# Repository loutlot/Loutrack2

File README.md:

# Loutrack2

Loutrack2 is an open-source optical motion tracking stack built around Raspberry Pi camera nodes, host-side calibration tools, and a GUI workflow that is already practical for multi-camera bring-up and tracking experiments.

日本語はこちら: [README_ja.md](README_ja.md)

## What It Is

Loutrack2 combines:

- Raspberry Pi camera capture nodes for reflective marker observation
- host-side control, calibration, and inspection tools
- multi-camera 3D reconstruction and tracking
- a GUI-first workflow for setup, tuning, capture, and review

This repository is aimed at people who want to build, understand, and extend a DIY camera-based tracking system in the open. The current project is strongest in camera bring-up, calibration, and live tracking inspection.

## What Works Today

- Pi capture nodes detect reflective blobs and stream observations to the host
- the host GUI covers blob tuning, mask building, pose capture, floor or metric capture, and extrinsics generation
- intrinsics and extrinsics outputs are generated as JSON artifacts
- synchronized camera observations are reconstructed into 3D marker positions
- the 3D Tracking page shows scene state, camera health, stream diagnostics, and live rigid-body status
- custom rigid bodies can be registered or removed directly from triangulated blobs in the tracking viewer

## System Overview

```mermaid
flowchart LR
  subgraph PiCameras["Raspberry Pi Camera Nodes"]
    A["pi-cam-01<br/>capture_runtime.py"]
    B["pi-cam-02+<br/>capture_runtime.py"]
    C["Blob detection<br/>Mask / Preview / UDP streaming"]
  end

  subgraph Host["Host Workstation"]
    D["loutrack_gui.py<br/>Web GUI"]
    E["UDPReceiver"]
    F["Calibration session"]
    G["Intrinsics / Extrinsics tools"]
    H["Tracking runtime"]
    I["3D reconstruction"]
  end

  subgraph Outputs["Outputs"]
    J["Intrinsics JSON"]
    K["Extrinsics JSON"]
    L["3D marker positions"]
    M["Tracking scene snapshot"]
  end

  A -->|UDP frames| E
  B -->|UDP frames| E
  D -->|TCP control| A
  D -->|TCP control| B
  E --> F
  F --> G
  G --> J
  G --> K
  E --> H
  H --> I
  I --> L
  H --> M
```

## Workflow

The current Loutrack2 experience is centered on a single GUI flow from camera startup to live tracking review.

Typical flow:

1. Start the Pi capture nodes
2. Open the host GUI
3. Tune blob detection
4. Build masks
5. Capture pose data
6. Capture floor or metric data
7. Generate extrinsics
8. Start tracking and inspect the reconstructed scene

The startup and shutdown procedure for Pi nodes and the GUI lives at [`docs/30_procedure/pi_gui_start_stop.md`](docs/30_procedure/pi_gui_start_stop.md).

## Tracking View

The 3D Tracking page is one of the clearest expressions of the project's current direction: operational feedback is visible, rigid bodies can be inspected live, and the scene is meant to be understandable while the system is running.

Current highlights:

- live tracking start and stop feedback is surfaced in the GUI
- camera health, latency, and stream diagnostics stay visible beside the scene
- the epipolar gate is adjustable from Tracking Control
- host tracking pairs frames with a fixed `4237us` half-frame window at `118fps`
- the old host-side sync-quality dashboard is gone, keeping tracking focused on scene and camera health
- custom rigid-body registration works directly from triangulated blobs

## Hardware Direction

Loutrack2 also includes an open hardware direction centered around reproducible DIY tracking camera nodes and tracked targets.

Current hardware direction:

- Raspberry Pi-based camera nodes built from commonly available parts
- Raspberry Pi Camera Module 3 Wide NoIR as the current camera baseline
- PoE HAT-based power and networking over a single LAN cable
- a custom board mounted above the Pi that combines camera holding and IR LED illumination
- open hardware files in the repository, including PCB design data and 3D-printable parts
- reflective tracked markers built from 3D-printed spheres and retroreflective tape

Relevant repository areas:

- [`hardware`](hardware) for printable parts and board-related assets
- [`hardware/LED board`](hardware/LED%20board) for the custom LED board design files
- [`hardware/pi mount`](hardware/pi%20mount) for Pi mount printable parts

## Project Direction

Loutrack2 is already useful as a multi-camera optical tracking foundation, but it is still a builder-oriented platform rather than a finished end-user full-body tracker.

The next direction includes:

- more stable rigid-body clustering and identity tracking
- body-part level tracking for head, chest, waist, and feet
- more reliable rigid-body association through the full pipeline
- IK-friendly pose output
- SteamVR tracker output
- continued improvements to deployment, setup, and hardware documentation

## Open Source

Loutrack2 is being developed in the open.

- pull requests are welcome
- forks and experiments are welcome
- documentation, setup improvements, hardware refinements, and calibration workflow improvements are especially useful

## License

This project is intended to be released under `GPL-3.0-or-later`.

## Repository Map

- [`src/pi`](src/pi) for Raspberry Pi capture services
- [`src/deploy`](src/deploy) for Raspberry Pi code deployment, service installation, and rollback helpers
- [`src/host`](src/host) for the host GUI, receiver, runtime, and tracking pipeline
- [`src/camera-calibration`](src/camera-calibration) for intrinsics and extrinsics tooling
- [`src/calibration`](src/calibration) for calibration domain types and targets
- [`calibration`](calibration) for generated calibration artifacts
- [`docs/30_procedure`](docs/30_procedure) for Pi / GUI startup, verification, and shutdown procedures
- [`schema`](schema) for message and control contracts
- [`tests`](tests) for regression coverage

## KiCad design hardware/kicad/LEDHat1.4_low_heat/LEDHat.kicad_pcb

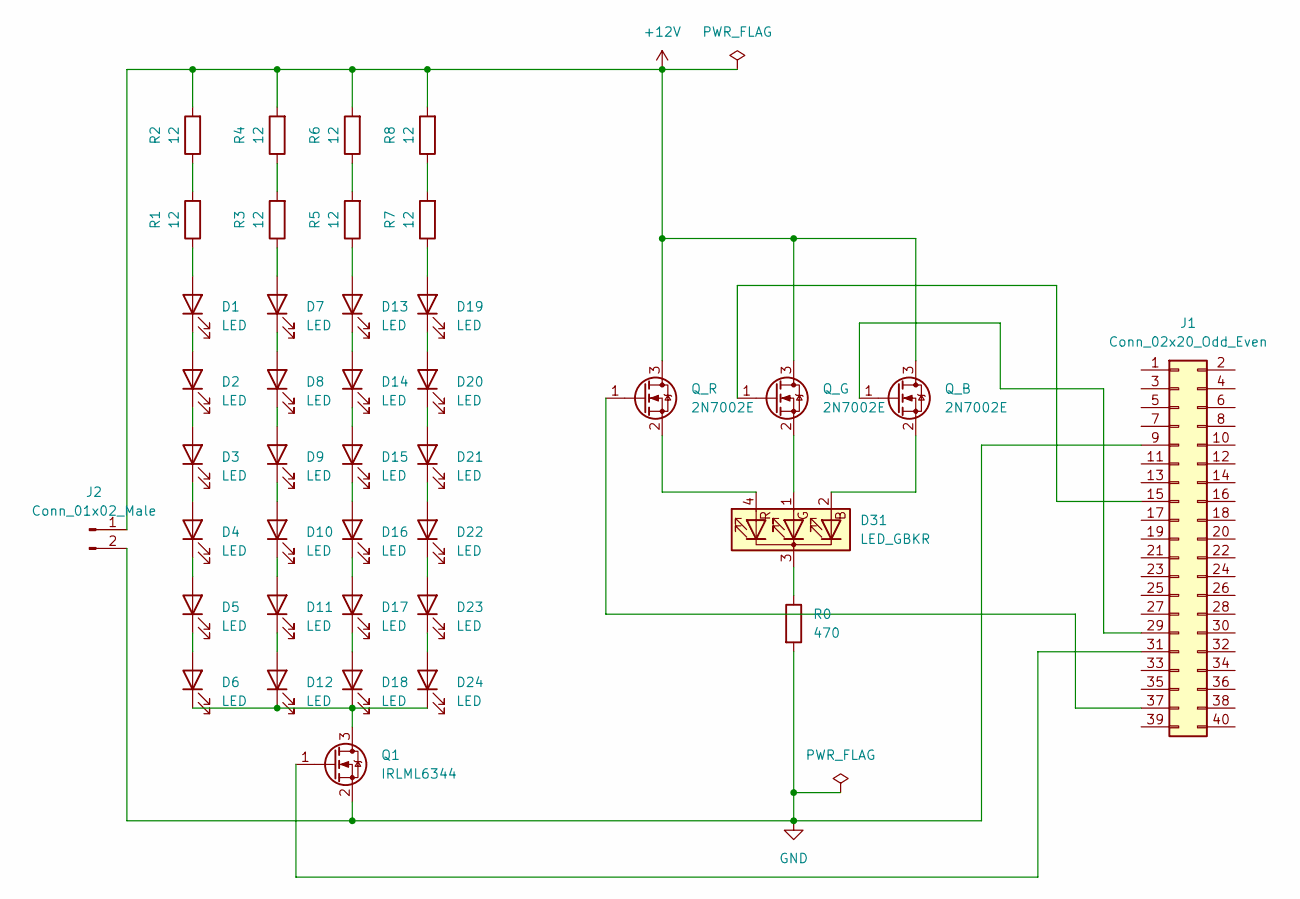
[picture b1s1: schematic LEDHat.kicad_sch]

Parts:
D1, D2, D3, D4, D5, D6, D7, D8, D9, D10, D11, D12, D13, D14, D15, D16, D17, D18, D19, D20, D21, D22, D23, D24: LED; LED_PLCC_2835_Handsoldering
D31: LED_GBKR; LED_D5.0mm-4_RGB_Staggered_Pins
J1: Conn_02x20_Odd_Even; PinSocket_2x20_P2.54mm_Vertical
J2: Conn_01x02_Male; PinHeader_1x02_P2.54mm_Horizontal
Q1: IRLML6344; SOT-23
Q_B: 2N7002E; SOT-23
Q_G: 2N7002E; SOT-23
Q_R: 2N7002E; SOT-23
R0: 470; R_Axial_DIN0207_L6.3mm_D2.5mm_P7.62mm_Horizontal
R1, R2, R3, R4, R5, R6, R7, R8: 12; R_Axial_DIN0207_L6.3mm_D2.5mm_P7.62mm_Horizontal

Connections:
+12V: J2.1, Q_B.3 (D), Q_G.3 (D), Q_R.3 (D), R2.2, R4.2, R6.2, R8.2
GND: J1.9, J2.2, Q1.2 (S), R0.2
unnamed: D1.1 (K), D2.2 (A)
unnamed: D1.2 (A), R1.1
unnamed: D2.1 (K), D3.2 (A)
unnamed: D3.1 (K), D4.2 (A)
unnamed: D4.1 (K), D5.2 (A)
unnamed: D5.1 (K), D6.2 (A)
unnamed: D7.1 (K), D8.2 (A)
unnamed: D7.2 (A), R3.1
unnamed: D8.1 (K), D9.2 (A)
unnamed: D10.1 (K), D11.2 (A)
unnamed: D9.1 (K), D10.2 (A)
unnamed: D11.1 (K), D12.2 (A)
unnamed: D6.1 (K), D12.1 (K), D18.1 (K), D24.1 (K), Q1.3 (D)
unnamed: D13.1 (K), D14.2 (A)
unnamed: D13.2 (A), R5.1
unnamed: D14.1 (K), D15.2 (A)
unnamed: D15.1 (K), D16.2 (A)
unnamed: D16.1 (K), D17.2 (A)
unnamed: D17.1 (K), D18.2 (A)
unnamed: D19.1 (K), D20.2 (A)
unnamed: D19.2 (A), R7.1
unnamed: D20.1 (K), D21.2 (A)
unnamed: D21.1 (K), D22.2 (A)
unnamed: D22.1 (K), D23.2 (A)
unnamed: D23.1 (K), D24.2 (A)
unnamed: D31.1 (GA), Q_G.2 (S)
unnamed: D31.2 (BA), Q_B.2 (S)
unnamed: D31.3 (K), R0.1
unnamed: D31.4 (RA), Q_R.2 (S)
unnamed: J1.15, Q_G.1 (G)
unnamed: J1.29, Q_B.1 (G)
unnamed: J1.31, Q1.1 (G)
unnamed: J1.37, Q_R.1 (G)
unnamed: R1.2, R2.1
unnamed: R3.2, R4.1
unnamed: R5.2, R6.1
unnamed: R7.2, R8.1

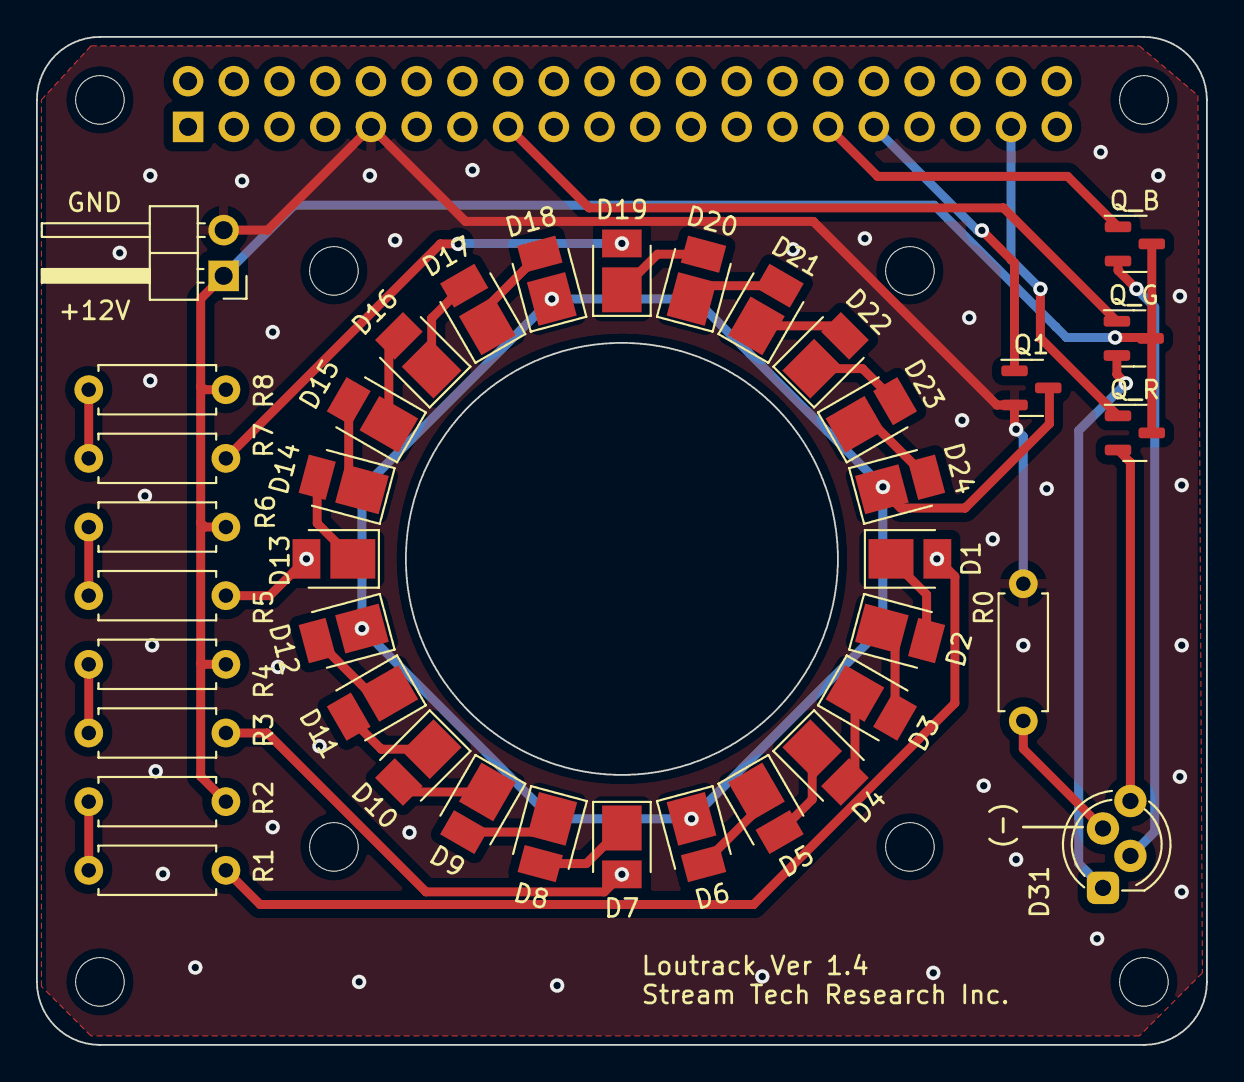
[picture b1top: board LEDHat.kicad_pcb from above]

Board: 2 copper layers, 65.0 x 56.0 mm, 40 parts (1 on the bottom side), 39 nets.

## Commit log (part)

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2026-02-22 chore: initial commit
2026-02-22 refactor: enhance Pi capture service and update control commands
    - Improved the Pi capture service in `src/pi/capture.py` for better performance.
    - Added new control commands (reset, get_status) in `src/host/control.py`.
    - Updated documentation to include new commands and usage examples.
2026-02-24 docs: remove outdated Pi service integration details from README and clean up hosts.ini comments
2026-03-07 feat: add wand session orchestration and next-step runbook
2026-03-08 feat: update default camera ID handling in capture service
    - Changed the default value of `camera_id` in `src/pi/capture.py` to derive from the device name using `hostnamectl` or fallback to `socket.gethostname()`.
    - Updated argument parsing in `parse_args()` to allow `--camera-id` to be optional, using the new default behavior if not specified.
    - Enhanced documentation in `README.md` to reflect these changes.
2026-03-08 feat: improve capture functionality and documentation for Pi and wand GUI
    - Enhanced `src/pi/capture.py` to disable debug preview automatically in headless environments to prevent crashes, and updated the default capture resolution to `2304x1296`.
    - Revised `src/host/wand_gui.py` to adjust console panel layout for better visibility of long JSON paths.
    - Updated documentation in `README.md`, `docs/next_steps_charuco.md`, and `docs/next_steps_wand_runbook.md` to reflect changes in capture resolution and debug preview handling.
    - Added tests for the new debug preview resolution logic in `tests/test_pi_blob_detector.py`.
2026-03-08 test
2026-03-08 Enhance debug preview handling and streamline mask overlay process in README and capture.py
2026-03-09 Add new 3D print models and LED board files for the project, including Ball.stl, base.stl, clamp1.stl, plate.stl, and various KiCad files for the LEDHat design. Remove outdated KiCad files to streaml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
2026-03-09 Revise README.md to provide a comprehensive overview of the Loutrack2 project, detailing the workflow, repository structure, and prerequisites for motion capture setup; enhance clarity for new users 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
2026-03-10 Update README.md and calibration scripts to reflect new wand geometry and confidence scoring system; enhance labeling process with temporal consistency checks and confidence thresholds; update schema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
2026-03-10 Enhance README.md with details on default downsampling for similarity solve in extrinsics calibration; update calibration JSON schema to include max BA samples; remove obsolete debug GIFs and JSONL l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
2026-03-13 Refactor extrinsics calibration process to focus solely on pose capture, removing wand metric capture from the workflow; update README.md with new instructions and JSON schema changes for extrinsics 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
2026-03-14 Enhance PTP setup and documentation by clarifying timestamping modes and improving error handling; update capture scripts to include role and timestamping mode in clock synchronization diagnostics; m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
2026-03-15 Add CLAUDE.md for project guidance and update .gitignore; modify extrinsics calibration scripts to include distortion coefficients in observations and improve triangulation process. Update README.md 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
2026-03-16 Refactor CLI auxiliary scripts by moving non-core capture functionalities from `src/host` to `src/host/auxiliary`. Update README.md and GUI runbook to reflect new script paths. Enhance JSON schema to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
2026-03-16 Enhance GUI and backend functionality for intrinsics calibration. Introduce new API commands for starting, stopping, clearing, calibrating, and checking the status of intrinsics capture. Update GUI t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
2026-03-24 Enhance intrinsics capture functionality and GUI responsiveness. Update README.md to reflect improvements in phase badge visibility and status synchronization. Modify JSON settings for calibration pa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
2026-03-24 Update loutrack_gui_settings.json to modify calibration parameters, including exposure, gain, focus, circularity, and mask threshold values for improved performance and consistency. Adjust timestamps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
2026-03-27 Update README.md and readmeja.md to include detailed descriptions of the current hardware direction for Loutrack2, outlining the Raspberry Pi-based camera nodes, their configurations, and relevant re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
2026-04-20 Enhance performance and diagnostics in tracking and capture systems
    - Updated README.md to reflect improvements in Pi blob-detection and host tracking-viewer integration, including optimizations for idle diagnostics and frame buffer management.
    - Modified `loutrack_gui.py` to improve JSON payload formatting for scene updates.
    - Enhanced `pipeline.py` to streamline pose processing and status tracking.
    - Improved `receiver.py` to ensure correct frame ordering and added methods for frame management.
    - Updated `tracking_runtime.py` to implement a short-lived status cache for efficient scene updates.
    - Enhanced `capture_runtime.py` to manage preview packet generation and diagnostics more effectiv
2026-04-21 Enhance tracking performance and diagnostics
    - Updated README.md to include new features in the tracking GUI, such as SSE scene updates and improved geometry diagnostics.
    - Modified `tracking_pipeline.py` to implement a 10 ms timestamp-only pairing window for frame matching, enhancing synchronization accuracy.
    - Improved `triangulator.py` to utilize one-to-one epipolar assignment for blob matching, preventing duplicate 3D point generation.
    - Adjusted `rigid.py` to refine clustering parameters for better rigid-body candidate selection.
    - Enhanced logging in `tracking_gui.jsonl` to capture detailed diagnostics and performance metrics.
    - Updated HTML and JavaScript in `index.html` to reflect ne
2026-04-22 Enhance triangulation quality metrics and diagnostics in tracking pipeline
    - Updated README.md to include new host-side raw 3D blob reconstruction features, emphasizing undistorted observation matching and robust multi-view inlier refinement.
    - Improved `geo.py` to refine epipolar and triangulation thresholds for precision-first tracking, and added new diagnostics for triangulation quality metrics.
    - Enhanced `pipeline.py` to incorporate updated triangulation quality summaries and diagnostics, including handling of low parallax candidates and dropped views for inlier fit.
    - Updated tests to validate new triangulation quality metrics and ensure accurate reporting of diagnostics across the tra
2026-04-23 STABLE: Update documentation and logging for Pi/GUI procedures and settings
    - Added a new section in `AGENTS.md` detailing the Pi/GUI startup and shutdown procedures.
    - Updated `README.md` to include the new documentation path for Pi/GUI procedures.
    - Revised `docs/README.md` to categorize documentation into operational procedures.
    - Enhanced logging in `loutrack_gui_server.log` to improve tracking diagnostics and error handling.
    - Adjusted `loutrack_gui_settings.json` to update calibration thresholds for improved consistency.
    - Refactored `tracking_gui.jsonl` to capture additional metrics and diagnostics for frame processing and synchronization.
2026-04-23 Enhance tracking viewer and rigid body management features
    - Introduced rectangle selection for registering and deleting custom rigid bodies in the tracking viewer, with persistence in `calibration/tracking_rigids.json`.
    - Updated host GUI to reflect new rigid body fitting constraints, enforcing a maximum RMS error of `0.055` for valid tracking poses.
    - Enhanced documentation in `README.md` and `README_ja.md` to include details on the new rigid body features and constraints.
    - Improved logging in `loutrack_gui_server.log` to capture additional tracking commands and diagnostics related to custom rigid bodies.
    - Adjusted settings in `loutrack_gui_settings.json` to accommodate the new rigid bod
2026-04-24 Phase0: Update tracking viewer features and calibration settings
    - The tracking viewer now hides the green origin dot while retaining the standard world-axis lines.
    - The Tracking Control card no longer displays the raw extrinsics file path banner.
    - Updated sidebar logo to use the new wordmark image instead of the compact badge.
    - Adjusted host tracking to use a fixed `4237 us` half-frame pair window at `118fps`, removing the sync-quality dashboard and adaptive pair-window logic.
    - Updated calibration settings and documentation to reflect these changes in `README.md` and `README_ja.md`.
2026-04-24 Phase 4: Implement Phase 4 2D reprojection scoring diagnostics
    - Added 2D reprojection scoring diagnostics to `RigidBodyEstimator` for enhanced tracking feedback.
    - Introduced `process_context()` method to handle 3D points with 2D observation context.
    - Updated `TrackingPipeline` to utilize the new scoring method, preserving existing pose acceptance logic.
    - Enhanced `RigidBodyTracker` to record and return reprojection scores without affecting tracking state.
    - Updated changelog to document the addition of Phase 4 diagnostics and their implications for tracking performance.
2026-04-24 Enhance Phase 5 Rigid Stabilization with Object-Conditioned Gating Diagnostics
    - Implemented diagnostics-only `rigid_hint` triangulation in Phase 5, allowing comparison with generic triangulation.
    - Updated `TrackingPipeline` to evaluate object-conditioned gating and record relevant events for diagnostics.
    - Enhanced `RigidBodyEstimator` to include object gating configuration and evaluation methods.
    - Added new data structures and summaries for object gating and rigid hint diagnostics in `TrackingReplaySummary`.
    - Documented changes in `changelog.md` to reflect advancements in Phase 5 features and their implications for rigid body stabilization.
2026-04-24 Enhance GUI Tracking with Rigid Stabilization Configuration
    - Updated the GUI to include a new `rigid_stabilization` configuration object, allowing for detailed control over stabilization parameters.
    - Modified the tracking service to forward the rigid stabilization settings during the start process.
    - Added tests to ensure the correct forwarding of rigid stabilization configurations and their integration into the tracking runtime.
    - Documented the changes in `changelog.md` to reflect the new GUI features and their implications for tracking diagnostics.
2026-04-25 PERFORMANCE UPDATE: Enhance Tracking Pipeline with Fast Geometry Support and Diagnostics
    - Introduced support for fast geometry in the tracking pipeline, allowing for baseline and fast_A-fast_ABCDE AB reports with improved performance metrics.
    - Updated the `Triangulator` class to include a fast geometry option, enhancing the efficiency of blob observations and triangulation processes.
    - Enhanced the tracking replay harness to accommodate new pipeline variants and diagnostics, improving the analysis of tracking performance.
    - Added detailed metrics for stage processing times and fallback reasons, facilitating better diagnostics during tracking operations.
    - Documented changes in `changelog.m
2026-04-25 Update GUI Tracking to Optimize Performance with Fast Path and Diagnostics
    - Set the official live path to `fast_ABCDHRF` for improved latency in GUI tracking.
    - Disabled subset diagnostics mode by default to enhance performance during live tracking.
    - Fully localized `performance_upgrade_log.md` in Japanese, maintaining benchmark paths and commands.
    - Updated `changelog.md` to reflect these changes and their impact on tracking diagnostics.
2026-04-28 Add skippable calibration instructions to Loutrack GUI
2026-04-29 Stabilize multi-rigid reacquire and ownership handling
2026-04-30 Refine cad fixtures and red stress simulation
